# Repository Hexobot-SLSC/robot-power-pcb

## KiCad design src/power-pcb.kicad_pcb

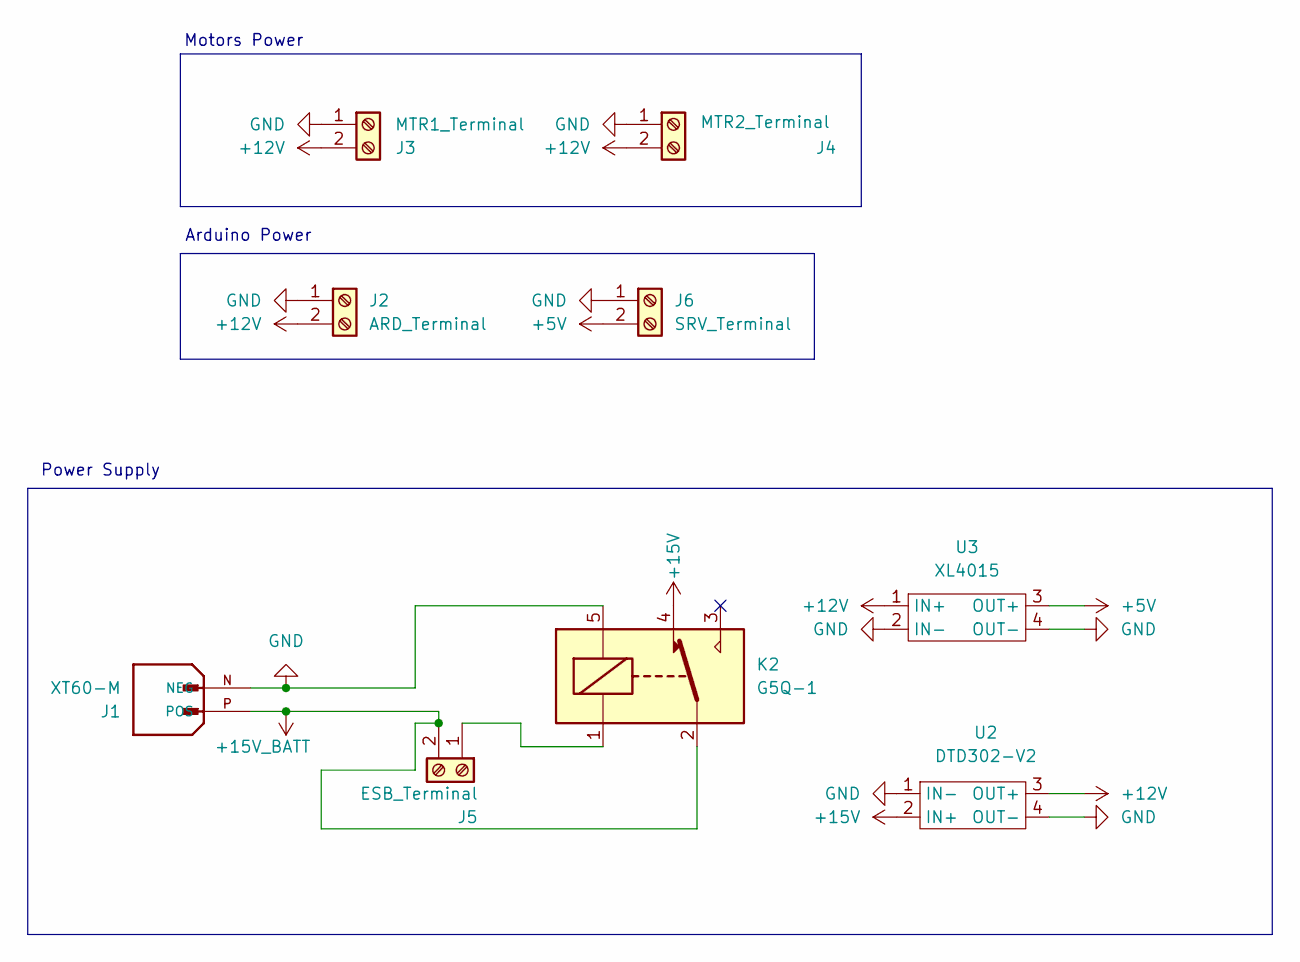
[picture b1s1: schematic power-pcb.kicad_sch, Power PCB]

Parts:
J1: XT60-M; AMASS_XT60-M; PARTREV V1.2
J2: ARD_Terminal; PhoenixContact_GMSTBA_2,5_2-G-7,62_1x02_P7.62mm_Horizontal
J3: MTR1_Terminal; PhoenixContact_GMSTBA_2,5_2-G-7,62_1x02_P7.62mm_Horizontal
J4: MTR2_Terminal; PhoenixContact_GMSTBA_2,5_2-G-7,62_1x02_P7.62mm_Horizontal
J5: ESB_Terminal; PhoenixContact_GMSTBA_2,5_2-G-7,62_1x02_P7.62mm_Horizontal
J6: SRV_Terminal; PhoenixContact_GMSTBA_2,5_2-G-7,62_1x02_P7.62mm_Horizontal
K2: G5Q-1; Relay_SPDT_Omron-G5Q-1
U2: DTD302-V2
U3: XL4015; L2596S

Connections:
+5V: J6.2, U3.3 (OUT+)
+12V: J2.2, J3.2, J4.2, U2.3 (OUT+), U3.1 (IN+)
+15V: K2.4, U2.2 (IN+)
+15V_BATT: J1.P (POS), J5.2, K2.2
GND: J1.N (NEG), J2.1, J3.1, J4.1, J6.1, K2.5, U2.1 (IN-), U2.4 (OUT-), U3.2 (IN-), U3.4 (OUT-)
unnamed: J5.1, K2.1

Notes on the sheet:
Motors Power
Arduino Power
Power Supply

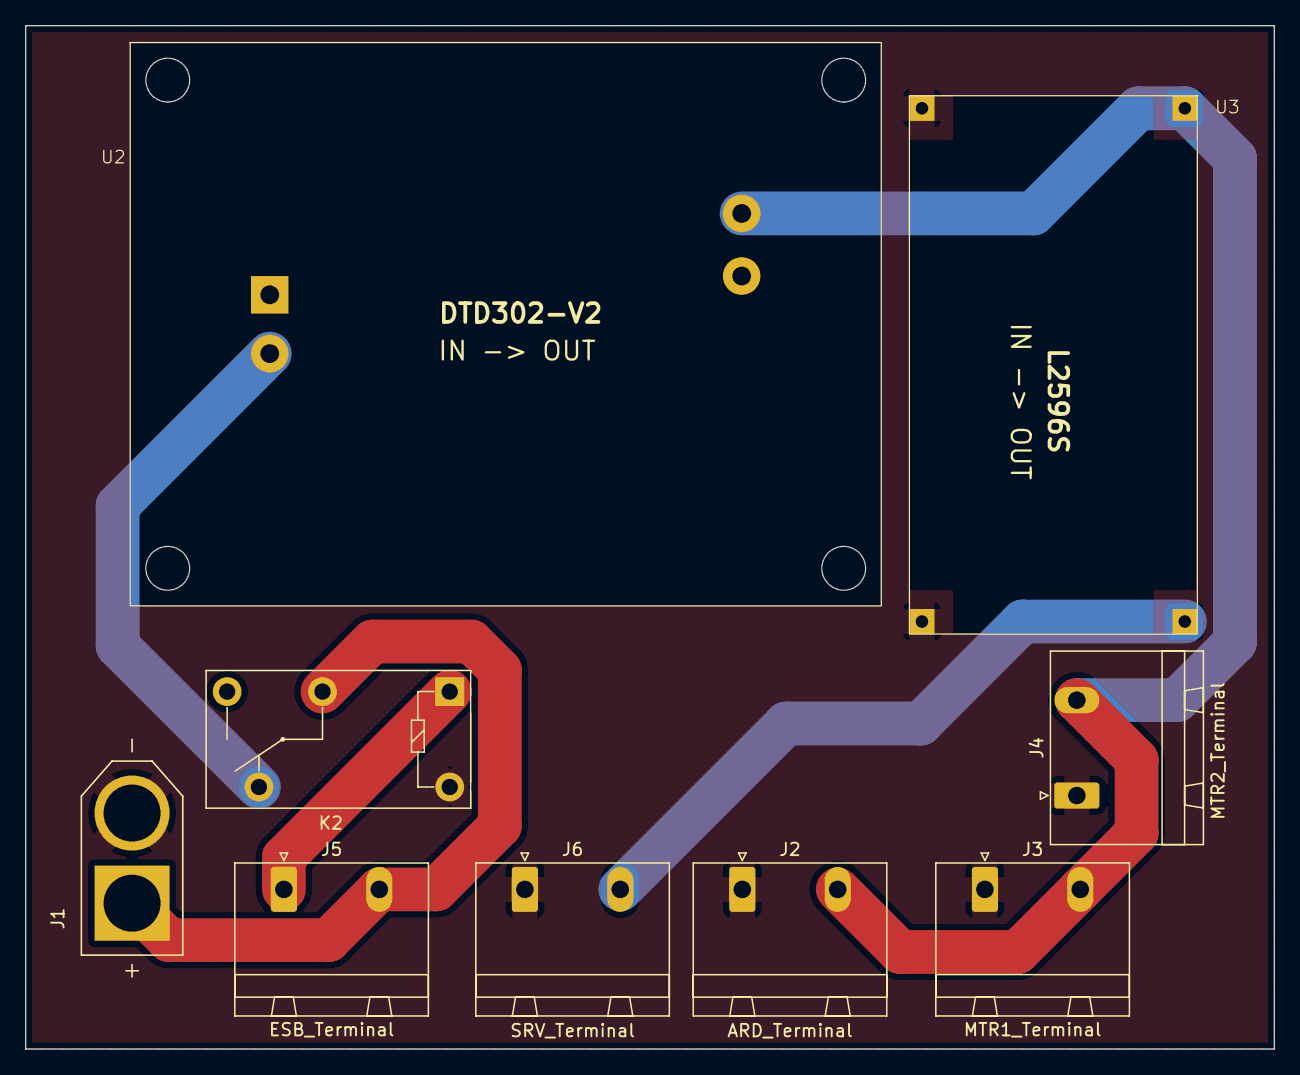
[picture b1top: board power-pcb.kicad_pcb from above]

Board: 2 copper layers, 99.8 x 81.8 mm, 9 parts (0 on the bottom side), 6 nets.

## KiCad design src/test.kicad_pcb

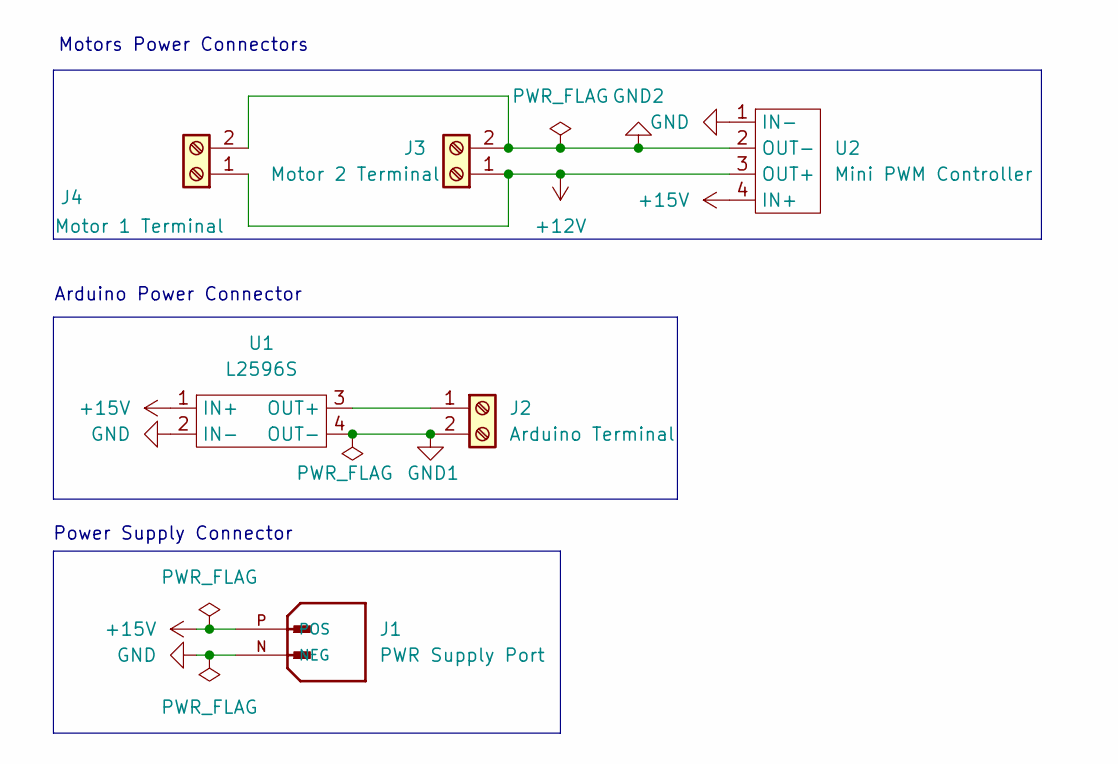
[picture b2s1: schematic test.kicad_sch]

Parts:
J1: PWR Supply Port; AMASS_XT60-M; PARTREV V1.2
J2: Arduino Terminal; TerminalBlock_Altech_AK300-2_P5.00mm
J3: Motor 2 Terminal; TerminalBlock_Altech_AK300-2_P5.00mm
J4: Motor 1 Terminal; TerminalBlock_Altech_AK300-2_P5.00mm
U1: L2596S
U2: Mini PWM Controller; Mini_PWM_Controller

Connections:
+12V: J3.1, J4.1, U2.3 (OUT+)
+15V: J1.P (POS), U1.1 (IN+), U2.4 (IN+)
GND: J1.N (NEG), U1.2 (IN-), U2.1 (IN-)
GND1: J2.2, U1.4 (OUT-)
GND2: J3.2, J4.2, U2.2 (OUT-)
unnamed: J2.1, U1.3 (OUT+)

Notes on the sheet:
Motors Power Connectors
Arduino Power Connector
Power Supply Connector

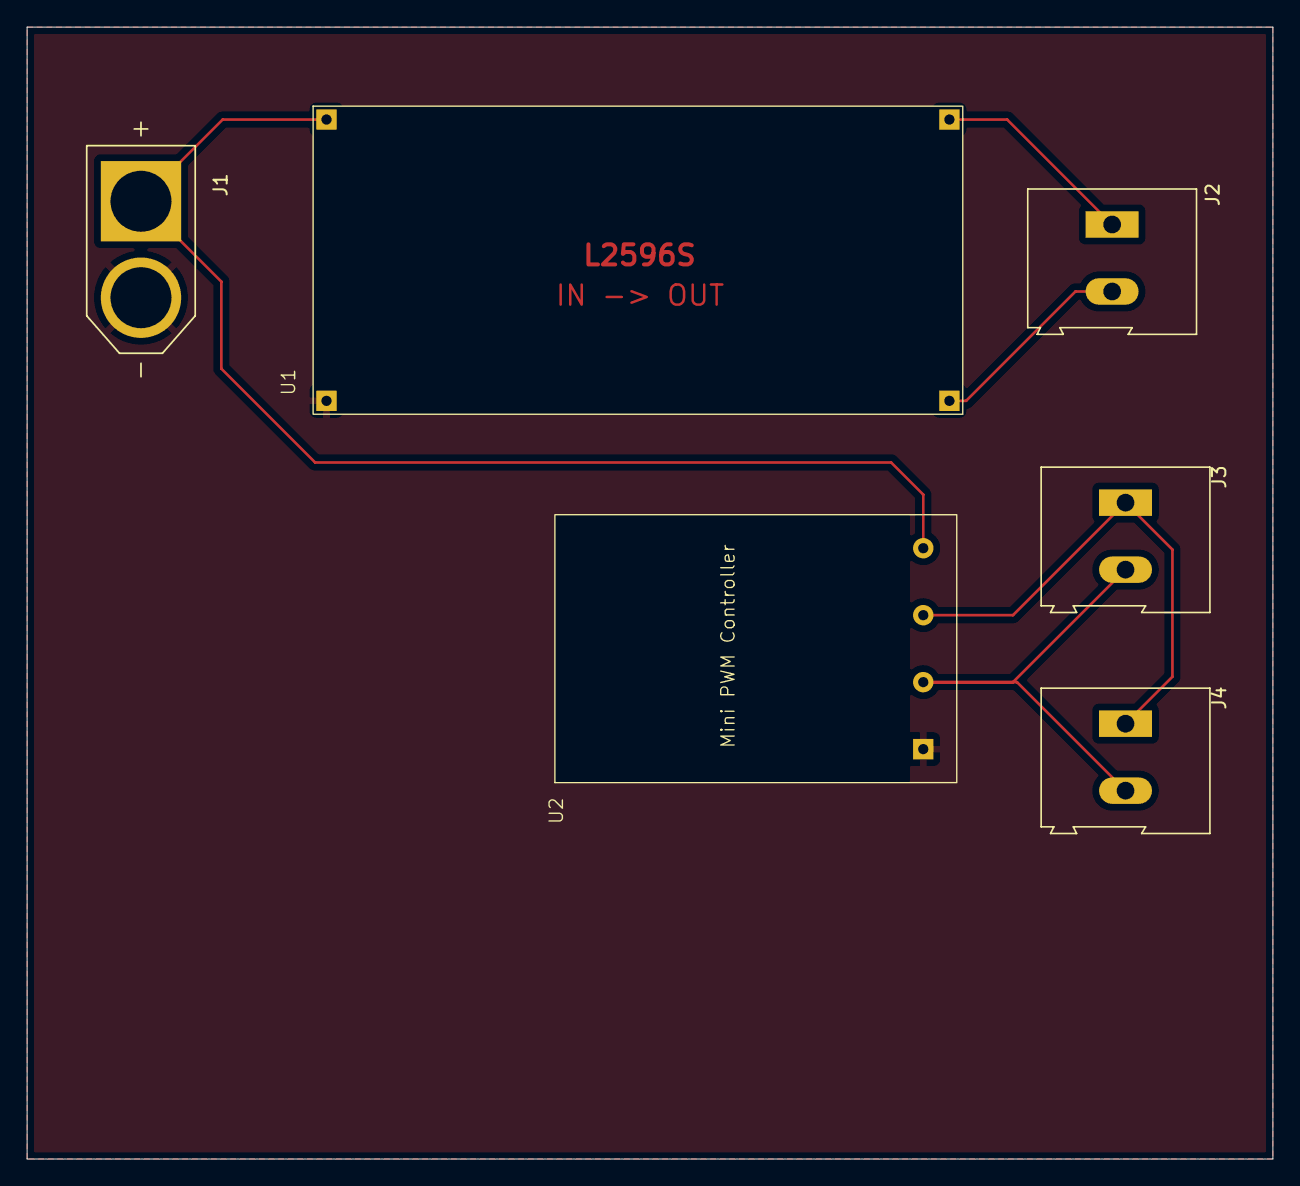
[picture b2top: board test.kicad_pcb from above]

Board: 2 copper layers, 93.0 x 84.5 mm, 6 parts (0 on the bottom side), 6 nets.

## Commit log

2024-04-03 Update of project
2024-04-03 Arduino and motors
2024-04-03 Add tracks
2024-04-03 Fix connections order on pwoer connectors
2024-04-08 Add relay
